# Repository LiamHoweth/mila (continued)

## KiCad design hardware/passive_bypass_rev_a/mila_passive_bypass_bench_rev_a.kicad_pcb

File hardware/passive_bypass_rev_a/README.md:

# MiLa passive bypass bench board — revision A

This is an isolated, current-limited simulator contact board. **No vehicle use.**
It preserves the three existing control domains and six passive NC paths using
four nonlatching Omron G6K-2P-Y DC5 relays. RLY3/RLY4 each use one pole; their
second poles are explicitly unconnected. K7/K8 independence is preserved.

## Electrical envelope and interfaces

- JPWR1 pin 1: regulated 4.75–5.25 V after an external physical series-enable
  switch. JPWR1 pin 2: logic/coil GND. Set the supply current limit to 150 mA.
- JCTRL1: 1 REQ_GROUP, 2 REQ_K7, 3 REQ_K8, 4 COIL_PERMIT, 5 GND,
  6 CARRIER_5V_FEEDBACK (direct connection to 5V_RAW). Digital inputs 1–4
  are active high and nominal 3.3 V, including COIL_PERMIT from the supervisor.
  Feedback pin 6 carries up to 5.25 V to the external
  resistor-divider monitor only; never connect it to an ESP GPIO or supply it.
  HIGH must be at least 2.60 V at the board header, LOW at most 0.4 V.
  All N-FET gates have 330-ohm series resistance. Q1–Q4 off bias is 10 kohm;
  Q6 permit-gate off bias RPD6 is 82 kohm, matched to the external supervisor's
  low-load LVC output guarantee. P-FET gate-to-source bias RPG1 stays 10 kohm.
  All carrier resistors require 1% tolerance, including RPD6; the gate-voltage
  bounds must not be extended to unspecified resistor substitutions.
- J4B1 is a 12-pin bench subset of original J4; JDAC1 is a 4-pin bench subset of
  original J5/J6. **Neither connector shares the original physical pinout.**
  Use `pin_net_map.csv`; names preserve canonical original connector terminals.
  Headers are unshrouded and unkeyed: mark pin 1, check the fixture orientation
  against the assembly drawing, and add cable strain relief before testing.
- Each contact signal is limited to 0–5 V and 1 mA on the simulator. Contacts
  do not connect to board GND. Provide source/load references externally.
- External independent supervisor supplies COIL_PERMIT. This board does not
  implement watchdog, freshness, boot/brownout qualification, DAC validation,
  dual-channel plausibility, or a vehicle safety case.
- No energy storage or external source may feed COIL_5V. The P-FET body diode
  does not provide reverse-current blocking. Its source is 5V_RAW and drain is
  COIL_5V; reversing it defeats the power cutoff.

## Operation

COIL_PERMIT low or disconnected turns off the common high-side coil feed.
With COIL_PERMIT high, REQ_GROUP energizes RLY1/RLY2, REQ_K7 RLY3, and REQ_K8
RLY4. Healthy unpowered contacts connect 3–2 and 6–7; energized contacts connect
3–4 and 6–5. Relay supply removal eventually restores NC after mechanical
release and bounce. This is not instantaneous or immune to welded contacts.

The supervisor senses JCTRL1 pin 6 through its divider. Complete loss of this
control header or JPWR1 power drops carrier feedback and clears its ARM latch;
reconnection requires a new valid heartbeat qualification and manual ARM edge.
This does not detect every individual broken conductor or intermittent fault.

Flyback diode cathodes connect to COIL_5V, anodes to their coil drains. These
diodes protect drivers but lengthen release. Measure release/bounce/skew on
the actual assembled board, including high-side cutoff with a low-side stuck
on. K7/K8 mixed states remain reachable and are not declared vehicle-safe.

## Manufacturer pinout and local footprint correction

G6K-2P-Y DC5 coil 1(+), 8(-); pole A COM 3/NC 2/NO 4; pole B COM 6/NC 7/NO 5.
The manufacturer bottom-view drawing gives hole rows 0, 3.2, 5.4, 7.6 mm and
opposing row spacing 5.08 mm. The installed KiCad 10 G6K-2P-Y footprint has
NC pads 2/7 at 3.0 mm; the project-local footprint corrects them to 3.2 mm.
Hole diameter 0.85 mm and pad diameter 1.7 mm. Inspect a 1:1 print and real
relay before ordering. All FETs use SOT-23 pins 1 gate, 2 source, 3 drain.

Manufacturer sources:

- [Omron G6K](https://omronfs.omron.com/en_US/ecb/products/pdf/en-g6k.pdf),
  manufacturer THT G6K-2P-Y drawing and terminal arrangement.
- [AO3400A](https://www.aosmd.com/res/data_sheets/AO3400A.pdf)
- [AO3401A](https://www.aosmd.com/res/data_sheets/AO3401A.pdf)
- [Vishay 1N4148W-E3-08](https://www.vishay.com/docs/86356/1n4148w.pdf)

## CAD and verification

The 60×50 mm, two-layer, 1.6-mm board uses 0.25-mm traces, 0.20-mm clearance,
0.70/0.30-mm vias, and four 3.2-mm unplated mounting holes. Mechanical contacts
are separated from logic by the relay insulation; no semiconductor is placed
in an NC/COM/NO signal path. Bench headers are 2.54-mm friction-fit prototypes,
not an automotive connector solution. The PCB is reviewed against the same
component/pin manifest that creates the editable schematic and BOM.

Rebuild with KiCad's bundled Python:

```sh
/Applications/KiCad/KiCad.app/Contents/Frameworks/Python.framework/Versions/3.9/bin/python3.9 tools/build_passive_bypass_board.py
```

Review `validation/erc.json`, `validation/drc.json` including schematic parity,
`passive_bypass.net`, and `validation/commands.json`. Bench manufacturing files
under `manufacturing_bench_only/` are exported only if ERC/DRC/netlist commands
pass. Electrical CAD checks do not establish relay behavior or vehicle safety.
Original PCB1/PCB2 files and libraries are preserved.

## Required assembled-board acceptance

1. Without any supply, map all six NC connections and confirm all NO paths
   open, contact-to-logic isolation, no misplaced/mirrored relay pins.
2. With simulator sources/load current limited, check all eight combinations
   of REQ_GROUP/REQ_K7/REQ_K8 under valid permit against the canonical table.
3. Drop each request, permit, series-enable, power, and logic source separately;
   capture contact disconnect/NC restoration, bounce, skew, and coil current.
4. Hold each low-side driver on and remove high-side permit; then force Q5 on
   and verify request removal still releases each coil. Neither single cutoff
   failure is declared fail-safe against a concurrent other-driver fault.
5. Sweep 4.75–5.25 V with maximum four-coil load. Check thermal rise and verify
   the external supervisor withdraws permit before coil behavior is ambiguous.
6. Inspect soldering/polarities; perform 100%-net continuity before sources are
   attached. Do not connect a vehicle when these bench tests pass.

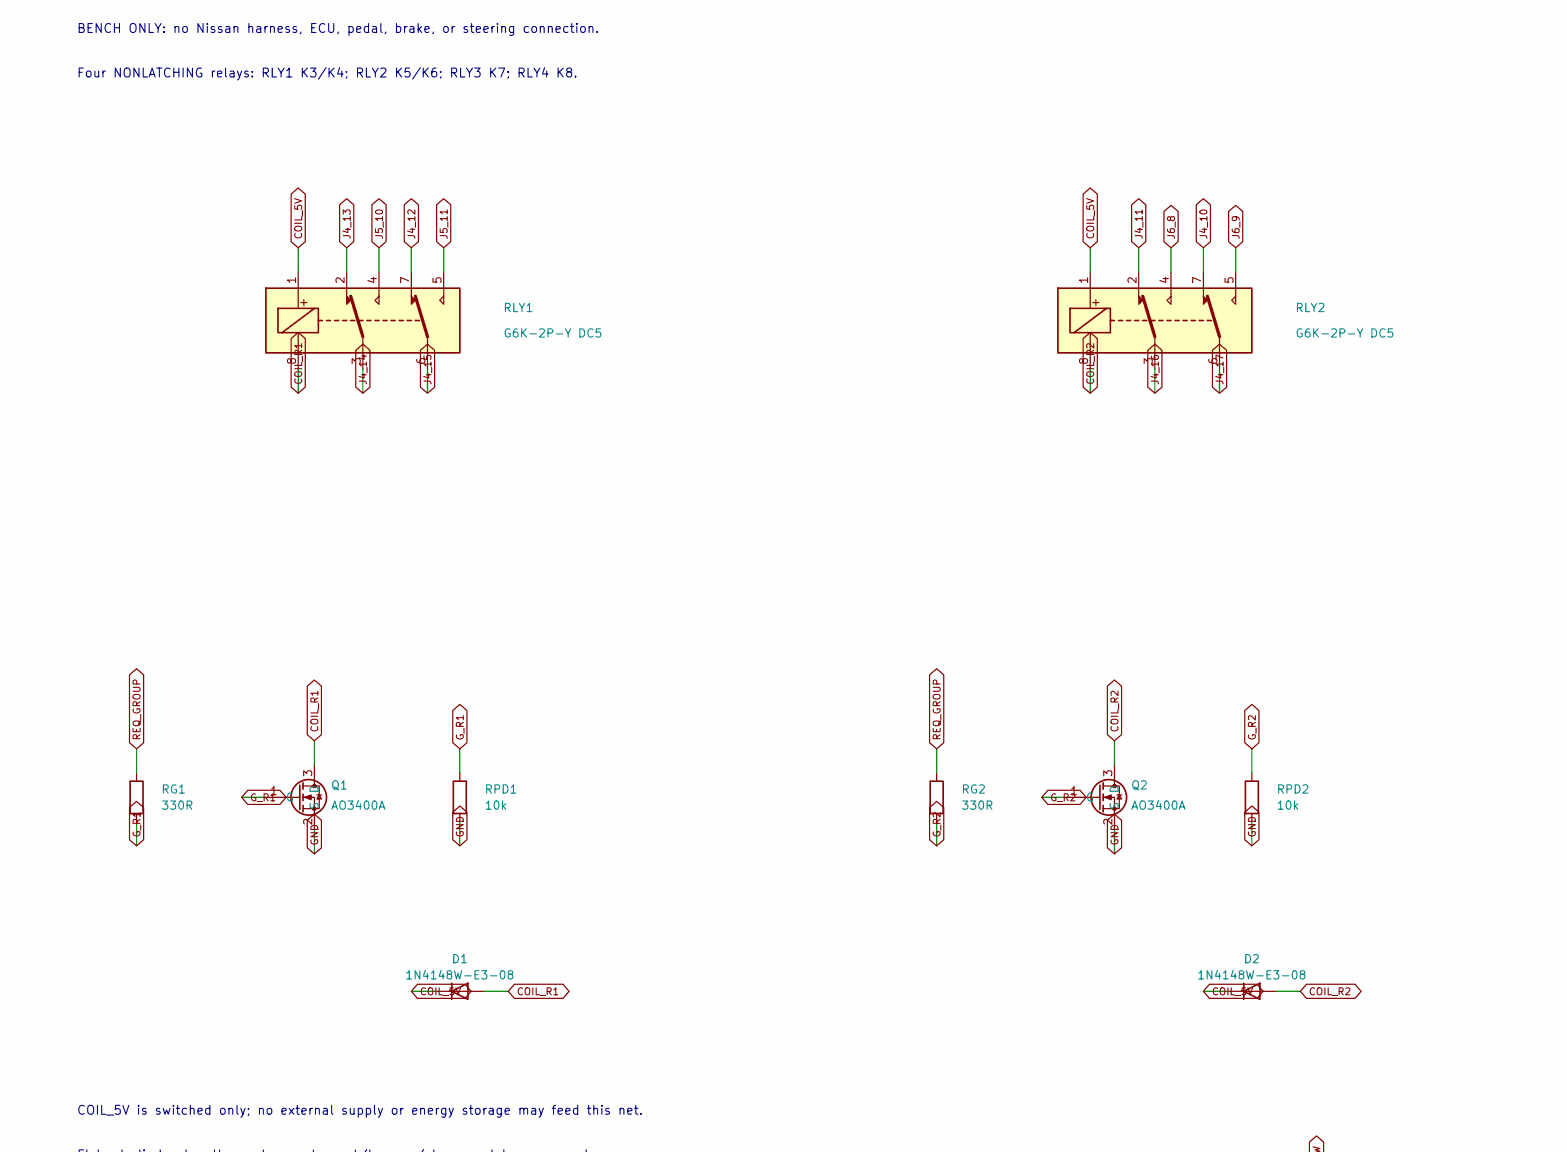
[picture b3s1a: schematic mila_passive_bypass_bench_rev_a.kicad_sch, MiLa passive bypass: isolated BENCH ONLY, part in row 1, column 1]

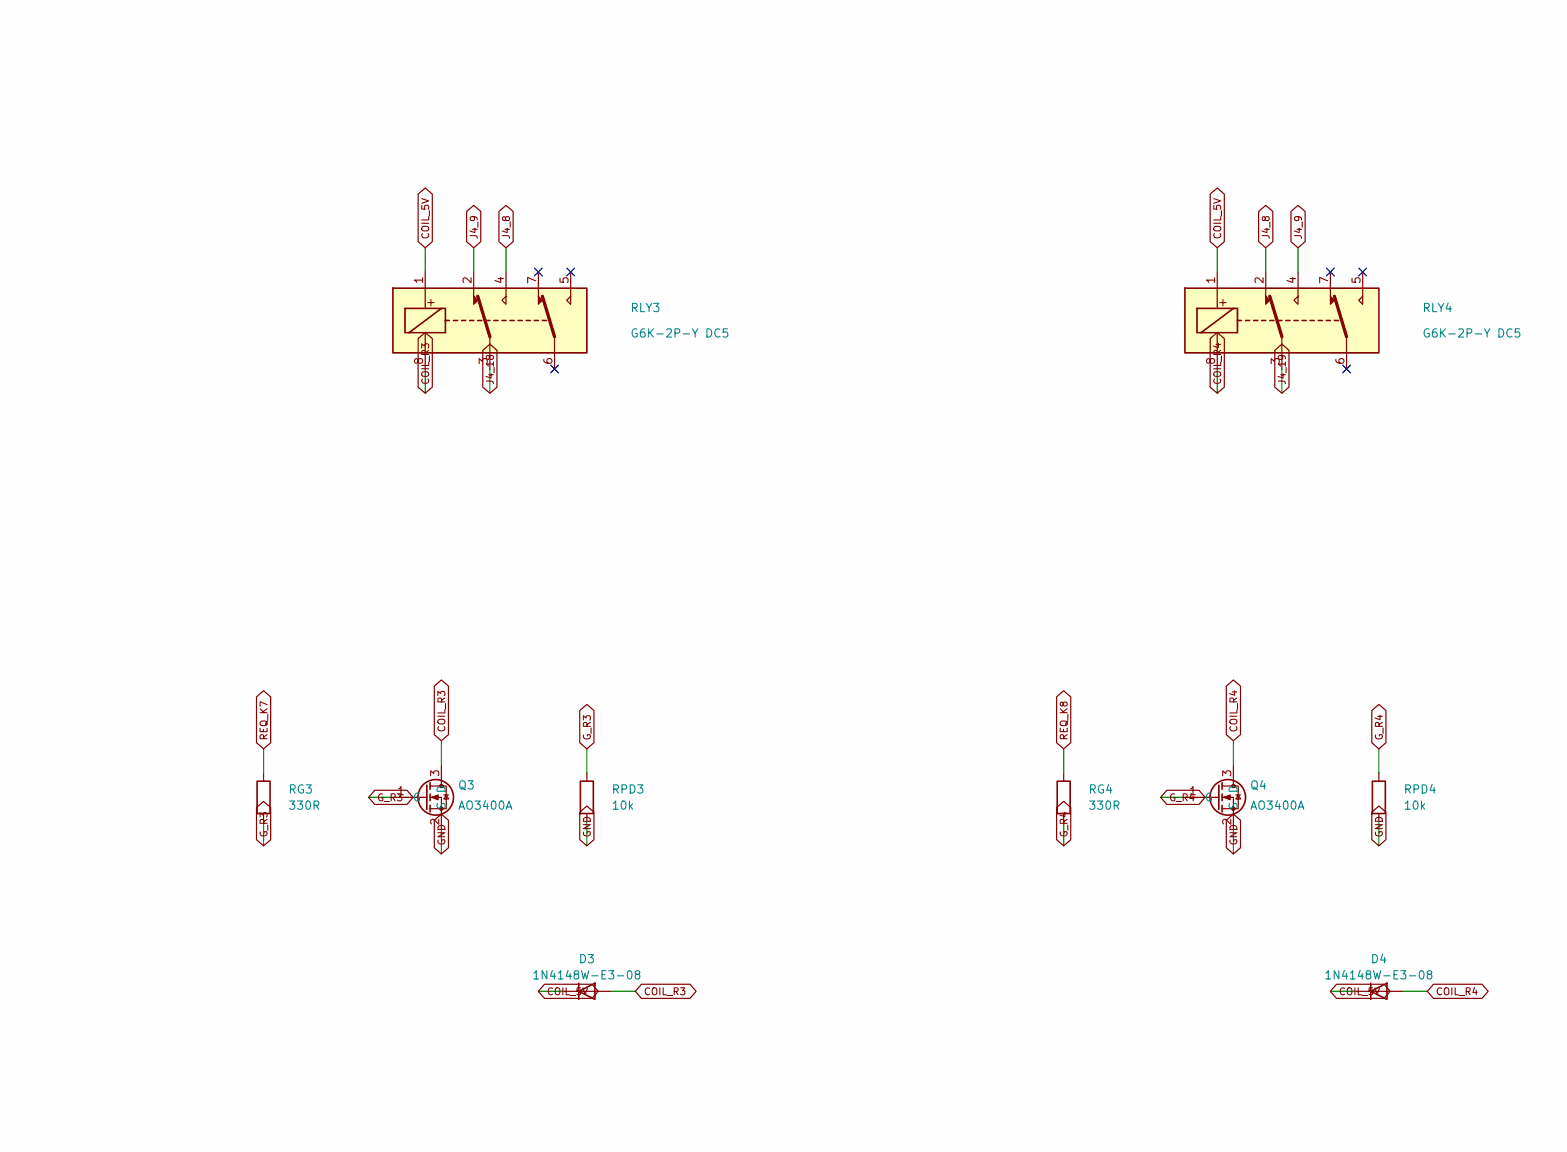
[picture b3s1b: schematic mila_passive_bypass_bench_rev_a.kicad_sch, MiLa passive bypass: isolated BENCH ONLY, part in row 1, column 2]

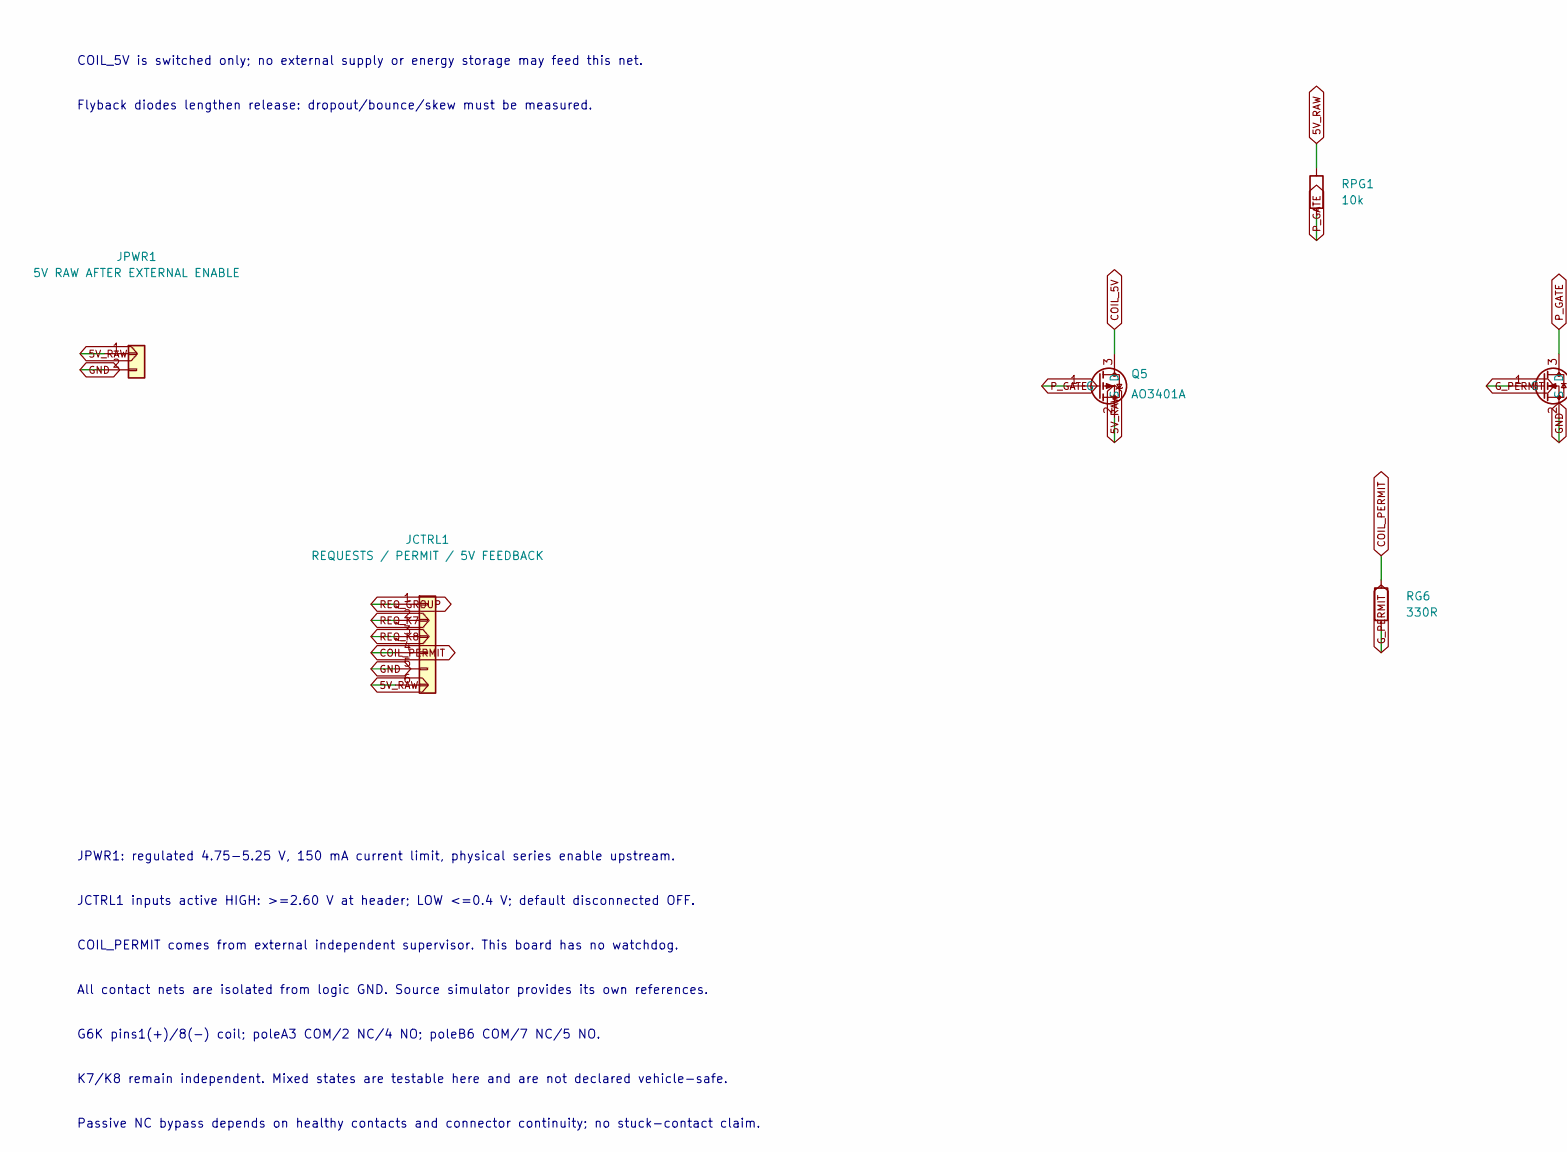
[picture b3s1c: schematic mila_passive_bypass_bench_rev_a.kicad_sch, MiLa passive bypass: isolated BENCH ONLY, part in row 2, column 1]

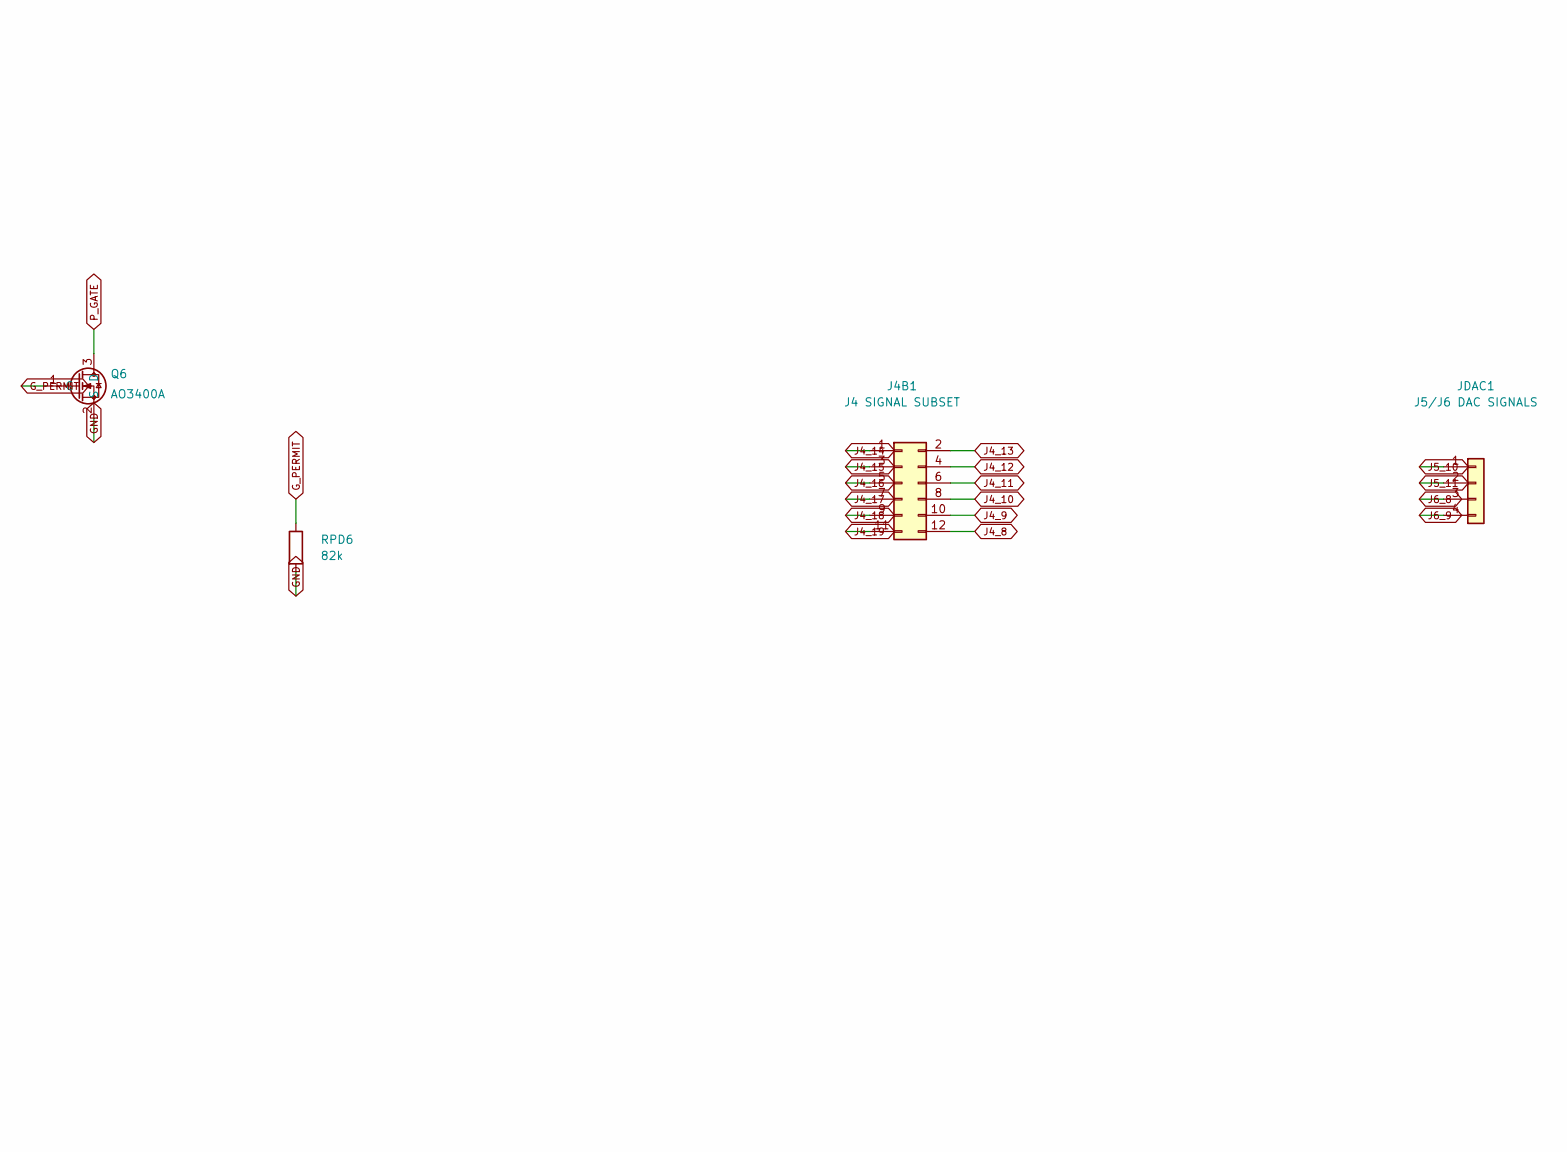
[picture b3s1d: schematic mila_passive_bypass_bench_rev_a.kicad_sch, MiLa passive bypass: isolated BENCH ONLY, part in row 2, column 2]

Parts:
D1, D2, D3, D4: 1N4148W-E3-08; D_SOD123
J4B1: J4 SIGNAL SUBSET; PinHeader_2x06
JCTRL1: REQUESTS / PERMIT / 5V FEEDBACK; PinHeader_1x06
JDAC1: J5/J6 DAC SIGNALS; PinHeader_1x04
JPWR1: 5V RAW AFTER EXTERNAL ENABLE; PinHeader_1x02
Q1, Q2, Q3, Q4, Q6: AO3400A; SOT-23
Q5: AO3401A; SOT-23
RG1, RG2, RG3, RG4, RG6: 330R; R_0805
RLY1, RLY2, RLY3, RLY4: G6K-2P-Y DC5; Relay_G6K_2P_Y_corrected
RPD1, RPD2, RPD3, RPD4: 10k; R_0805
RPD6: 82k; R_0805
RPG1: 10k; R_0805

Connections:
5V_RAW: JCTRL1.6, JPWR1.1, Q5.2 (S), RPG1.1
COIL_5V: D1.1 (K), D2.1 (K), D3.1 (K), D4.1 (K), Q5.3 (D), RLY1.1, RLY2.1, RLY3.1, RLY4.1
COIL_PERMIT: JCTRL1.4, RG6.1
COIL_R1: D1.2 (A), Q1.3 (D), RLY1.8
COIL_R2: D2.2 (A), Q2.3 (D), RLY2.8
COIL_R3: D3.2 (A), Q3.3 (D), RLY3.8
COIL_R4: D4.2 (A), Q4.3 (D), RLY4.8
GND: JCTRL1.5, JPWR1.2, Q1.2 (S), Q2.2 (S), Q3.2 (S), Q4.2 (S), Q6.2 (S), RPD1.2, RPD2.2, RPD3.2, RPD4.2, RPD6.2
G_PERMIT: Q6.1 (G), RG6.2, RPD6.1
G_R1: Q1.1 (G), RG1.2, RPD1.1
G_R2: Q2.1 (G), RG2.2, RPD2.1
G_R3: Q3.1 (G), RG3.2, RPD3.1
G_R4: Q4.1 (G), RG4.2, RPD4.1
J4_8: J4B1.12, RLY3.4, RLY4.2
J4_9: J4B1.10, RLY3.2, RLY4.4
J4_10: J4B1.8, RLY2.7
J4_11: J4B1.6, RLY2.2
J4_12: J4B1.4, RLY1.7
J4_13: J4B1.2, RLY1.2
J4_14: J4B1.1, RLY1.3
J4_15: J4B1.3, RLY1.6
J4_16: J4B1.5, RLY2.3
J4_17: J4B1.7, RLY2.6
J4_18: J4B1.9, RLY3.3
J4_19: J4B1.11, RLY4.3
J5_10: JDAC1.1, RLY1.4
J5_11: JDAC1.2, RLY1.5
J6_8: JDAC1.3, RLY2.4
J6_9: JDAC1.4, RLY2.5
P_GATE: Q5.1 (G), Q6.3 (D), RPG1.2
REQ_GROUP: JCTRL1.1, RG1.1, RG2.1
REQ_K7: JCTRL1.2, RG3.1
REQ_K8: JCTRL1.3, RG4.1

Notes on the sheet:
BENCH ONLY: no Nissan harness, ECU, pedal, brake, or steering connection.
Four NONLATCHING relays: RLY1 K3/K4; RLY2 K5/K6; RLY3 K7; RLY4 K8.
COIL_5V is switched only; no external supply or energy storage may feed this net.
Flyback diodes lengthen release: dropout/bounce/skew must be measured.
JPWR1: regulated 4.75-5.25 V, 150 mA current limit, physical series enable upstream.
JCTRL1 inputs active HIGH: >=2.60 V at header; LOW <=0.4 V; default disconnected OFF.
COIL_PERMIT comes from external independent supervisor. This board has no watchdog.
All contact nets are isolated from logic GND. Source simulator provides its own references.
G6K pins1(+)/8(-) coil; poleA3 COM/2 NC/4 NO; poleB6 COM/7 NC/5 NO.
K7/K8 remain independent. Mixed states are testable here and are not declared vehicle-safe.
Passive NC bypass depends on healthy contacts and connector continuity; no stuck-contact claim.

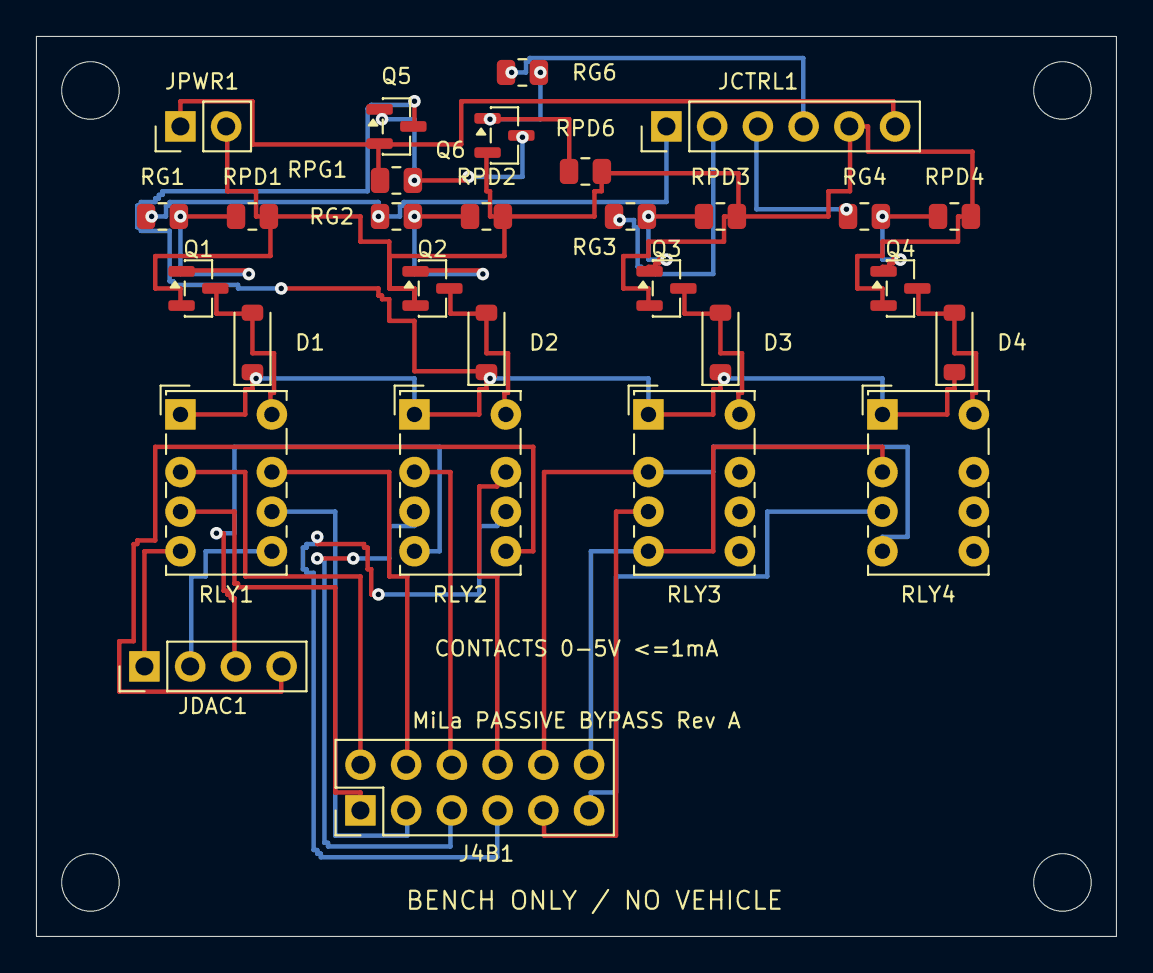
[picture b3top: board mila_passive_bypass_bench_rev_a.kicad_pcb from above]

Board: 2 copper layers, 60.0 x 50.0 mm, 33 parts (0 on the bottom side), 33 nets.

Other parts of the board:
H1, H2, H3, H4: MountingHole_3.2mm

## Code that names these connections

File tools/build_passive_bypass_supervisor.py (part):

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
add("U1", "TPS3430WQDRCRQ1", "Independent window watchdog; fixed hardware settings",
    "Package_SON:VSON-10-1EP_3x3mm_P0.5mm_EP1.65x2.4mm", WD,
    [pin(1,"VDD1","V3V3","power_in"),pin(2,"CWD","WD_CWD"),pin(3,"SET0","GND"),
     pin(4,"CRST","WD_CRST"),pin(5,"GND","GND","power_in"),pin(6,"SET1","GND"),
     pin(7,"WDI","WDI"),pin(8,"WDO_N","HEALTH_N","open_collector"),
     pin(9,"NC",None,"no_connect"),pin(10,"VDD2","V3V3","power_in"),pin(11,"EP","GND","passive")], 180,60)
add("U2","TPS3808G33QDBVRQ1","3.3 V and ESP hardware reset supervisor", "Package_TO_SOT_SMD:SOT-23-6",SUP,
    [pin(1,"RESET_N","HEALTH_N","open_collector"),pin(2,"GND","GND","power_in"),
     pin(3,"MR_N","ESP_RESET_N"),pin(4,"CT","PG33_CT"),pin(5,"SENSE","V3V3"),pin(6,"VDD","V3V3","power_in")], 300,60)
add("U3","TPS3808G01QDBVRQ1","5 V adjustable monitor supplied by isolated diode-OR of both rails", "Package_TO_SOT_SMD:SOT-23-6",SUP,
    [pin(1,"RESET_N","HEALTH_N","open_collector"),pin(2,"GND","GND","power_in"),
     pin(3,"MR_N","V_PG5_SUP"),pin(4,"CT","PG5_CT"),pin(5,"SENSE","V5_SENSE"),pin(6,"VDD","V_PG5_SUP","power_in")], 420,60)
add("D1","BAS70-05-7-F","Low-leakage supply OR keeps 5 V monitor alive when either rail disappears", "Package_TO_SOT_SMD:SOT-23",DIODE,
    [pin(1,"A1","V3V3","passive"),pin(2,"A2","V5_SUP","passive"),pin(3,"K1_K2","V_PG5_SUP","passive")], 780,60)


def schmitt(ref, role, a, y, x, yy):
    return add(ref,"SN74LVC1G17QDCKRQ1",role,SC5,BUF,
        [pin(1,"NC",None,"no_connect"),pin(2,"A",a),pin(3,"GND","GND","power_in"),
         pin(4,"Y",y,"output"),pin(5,"VCC","V3V3","power_in")],x,yy)


schmitt("U4","Clean open-drain fault edges before ordinary logic","HEALTH_N","HEALTH_OK",540,60)
schmitt("U5","Clean physical enable auxiliary-contact edges","DEADMAN_RAW","DEADMAN_OK",660,60)
add("U6","SN74LVC2G14IDCKRQ1","Invert WDI falling edges and debounce physical ARM",SC6,INV,
    [pin(1,"1A","WDI"),pin(2,"GND","GND","power_in"),pin(3,"2A","ARM_RC"),
     pin(4,"2Y","ARM_CLK","output"),pin(5,"VCC","V3V3","power_in"),pin(6,"1Y","HB_CLK","output")], 60,150)
add("U7","SN74LVC1G27DCKR","All three relay requests must be LOW at ARM edge; catalog bench part",SC6,NOR,
    [pin(1,"A","REQ_L"),pin(2,"GND","GND","power_in"),pin(3,"B","REQ_7"),
     pin(4,"Y","ZERO_REQ","output"),pin(5,"VCC","V3V3","power_in"),pin(6,"C","REQ_8")],180,150)


def and_gate(ref, role, a, b, y, x, yy):
    return add(ref,"SN74LVC1G08QDCKRQ1",role,SC5,AND,
        [pin(1,"A",a),pin(2,"B",b),pin(3,"GND","GND","power_in"),
         pin(4,"Y",y,"output"),pin(5,"VCC","V3V3","power_in")],x,yy)


and_gate("U8","Combine rail/watchdog health and firmware READY","HEALTH_OK","READY","HEALTH_READY",300,150)
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
def flipflop(ref, role, clock1, data1, out1, clock2, data2, out2, x, yy, unused2=False):
    return add(ref,"SN74LVC74AQPWRG4Q1",role,TS14,FF,
       [pin(1,"1CLR_N","QUALIFIED"),pin(2,"1D",data1),pin(3,"1CLK",clock1),
        pin(4,"1PRE_N","V3V3"),pin(5,"1Q",out1,"output"),pin(6,"1Q_N",None,"output"),
        pin(7,"GND","GND","power_in"),pin(8,"2Q_N",None,"output"),pin(9,"2Q",out2,"output"),
        pin(10,"2PRE_N","V3V3"),pin(11,"2CLK",clock2),pin(12,"2D",data2),
        pin(13,"2CLR_N","GND" if unused2 else "QUALIFIED"),pin(14,"VCC","V3V3","power_in")],x,yy)


flipflop("U10","Two WDI falling edges after READY/enable; one full inter-edge cycle",
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        [pin(i+1,n,n,"passive") for i,n in enumerate(nets)],x,yy)


header("J1","ESP interface: shared 3.3 V rail, no GPIO mapping assumed",["GND","V3V3","ESP_RESET_HEADER","WDI_HEADER","READY_HEADER","REQ_L","REQ_7","REQ_8"],60,60)
header("J2","Protected regulated bench 5 V upstream rail",["V5_SUP","GND"],300,240)
header("J3","External held enable: pole A 1-2 physically cuts coil feed; pole B 3-4 reports enable",["V5_SUP","V5_COIL_SWITCHED","V3V3","DEADMAN_HEADER"],420,240)
header("J4","Physical normally-open ARM pushbutton shorts 1-2 only",["ARM_SW","GND"],540,240)
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for ref,val,role,a,b in [
    ("R1","10k 1%","Watchdog fixed window setting","V3V3","WD_CWD"),
    ("R2","10k 1%","Watchdog fixed reset setting","V3V3","WD_CRST"),
    ("R3","100k 1%","300 ms nominal PG33 reset release","V3V3","PG33_CT"),
    ("R4","100k 1%","300 ms nominal PG5 reset release","V_PG5_SUP","PG5_CT"),
    ("R5","10k 1%","Shared open-drain health pull-up","V3V3","HEALTH_N"),
    ("R6","100k 1%","ARM default released; 100 ms nominal release RC","V3V3","ARM_RC"),
    ("R7","1k 1%","ARM press current/RC limit","ARM_RC","ARM_SW"),
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    ("R11","10k 1%","Relay request default LOW","REQ_L","GND"),
    ("R12","10k 1%","Relay request default LOW","REQ_7","GND"),
    ("R13","10k 1%","Relay request default LOW","REQ_8","GND"),
    ("R14","100 1%","Short local WDI wire series damping","WDI_HEADER","WDI"),
    ("R15","100 1%","Short local READY wire series damping","READY_HEADER","READY"),
    ("R16","1k 1%","ESP hardware reset input current limit","ESP_RESET_HEADER","ESP_RESET_N"),
    ("R17","100 1%","Physical enable sense series damping","DEADMAN_HEADER","DEADMAN_RAW"),
    ("R18","1k 1%","Permit initial MOS gate-current limit and series damping","PERMIT_DRIVER","COIL_PERMIT"),
    ("R19","82k 1%","Light permission load; parallel carrier 82k provides passive LOW","COIL_PERMIT","GND"),
    ("R20","10k 1%","Permit-gate ARMED input passive LOW","ARMED","GND"),
    ("R21","10k 1%","Permit-gate QUALIFIED input passive LOW","QUALIFIED","GND"),
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passive("C16","1uF X7R 10V","Upstream 5 V local decoupling; not downstream of enable switch","V5_SUP","GND")
passive("C17","1nF C0G 10V","5 V SENSE divider noise filter; ~8.7 us nominal RC","V5_SENSE","GND")
passive("C18","100pF C0G 5% 10V","Heartbeat stage delay; ~100 ns nominal RC before Schmitt buffer","HB_STAGE_RC","GND")
passive("C19","100nF X7R 10V","Place at U14 supply pin","V3V3","GND")

for i,p in enumerate([p for p in parts if p.ref[0] in "RC"]):
    p.x=50 + (i%10)*77
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
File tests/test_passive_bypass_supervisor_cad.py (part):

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        if not values[self.pin("U11", 1)]:
            armed = False
        state = (hb_one, hb_good, armed)
        values[self.pin("U10", 5)] = hb_one
        values[self.pin("U10", 9)] = hb_good
        values[self.pin("U11", 5)] = armed

        # The R24/C18 node and U14 noninverting Schmitt buffer are identities
        # after settling. This makes no claim about their physical delay.
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            self.assertEqual(self.circuit.parts[ref], "SN74LVC1G08QDCKRQ1")
        for ref in ("U10", "U11"):
            for pin in (4, 10, 14):
                self.assertEqual(self.circuit.pin(ref, pin), "V3V3")
            self.assertEqual(self.circuit.pin(ref, 7), "GND")
        for pin in (11, 12, 13):
            self.assertEqual(self.circuit.pin("U11", pin), "GND")
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            ("U3", 1): "HEALTH_N", ("U3", 2): "GND",
            ("U3", 3): "V_PG5_SUP", ("U3", 5): "V5_SENSE",
            ("U3", 6): "V_PG5_SUP",
            ("R4", 1): "V_PG5_SUP", ("R4", 2): "PG5_CT",
            ("R22", 1): "CARRIER_5V_FEEDBACK", ("R22", 2): "V5_SENSE",
            ("R23", 1): "V5_SENSE", ("R23", 2): "GND",
            ("C3", 1): "V_PG5_SUP", ("C3", 2): "GND",
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
    def test_permit_output_drive_and_physical_coil_feed_are_separate(self):
        self.assertEqual(self.circuit.parts["R18"], "1k 1%")
        self.assertEqual(self.circuit.pin("R18", 1), "PERMIT_DRIVER")
        self.assertEqual(self.circuit.pin("R18", 2), "COIL_PERMIT")
        self.assertEqual(self.circuit.pin("R19", 1), "COIL_PERMIT")
        self.assertEqual(self.circuit.pin("R19", 2), "GND")
        self.assertEqual(self.circuit.parts["R19"], "82k 1%")
        self.assertEqual(self.circuit.pin("C13", 1), "V3V3")
        self.assertEqual(self.circuit.pin("C13", 2), "GND")
        # Including carrier RG6=330 ohm, initial gate-current upper bound is
        # below the LVC output recommendation. This is a resistor calculation.
        self.assertLess(3.6 / ((1000 + 330) * 0.99), 0.024)
        self.assertEqual(self.circuit.pin("J3", 1), "V5_SUP")
        self.assertEqual(self.circuit.pin("J3", 2), "V5_COIL_SWITCHED")
        self.assertEqual(self.circuit.pin("J5", 2), "V5_COIL_SWITCHED")
        self.assertEqual(self.circuit.pin("J5", 3), "COIL_PERMIT")
        # The external deadman contact, not a copper short in this schematic,
        # joins J3 pins1/2. Permission is not exposed on the ESP header J1.
        self.assertNotEqual(self.circuit.pin("J3", 1), self.circuit.pin("J3", 2))
        self.assertNotIn(
            "COIL_PERMIT", [self.circuit.pin("J1", pin) for pin in range(1, 9)]
        )

    def permit_resistors(self):
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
